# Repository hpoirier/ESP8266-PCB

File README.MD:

Multi application PCB

PCB based on ESP8266 for
- Weather Station: low consumption, can be put in deep sleep and wake up at regular intervals or on an event
- Relay control, for roller blinds for example

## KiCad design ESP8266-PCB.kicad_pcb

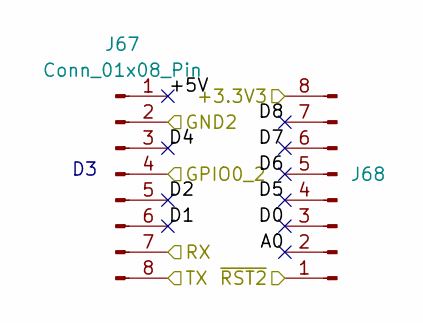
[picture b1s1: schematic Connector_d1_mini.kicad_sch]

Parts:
J67, J68: Conn_01x08_Pin; PinHeader_1x08_P2.54mm_Vertical

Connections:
/+3.3V3: J68.8; also elsewhere on the board
/Connector_d1_mini/+5V: J67.1
/Connector_d1_mini/A0: J68.2
/Connector_d1_mini/D0: J68.3
/Connector_d1_mini/D1: J67.6
/Connector_d1_mini/D2: J67.5
/Connector_d1_mini/D4: J67.3
/Connector_d1_mini/D5: J68.4
/Connector_d1_mini/D6: J68.5
/Connector_d1_mini/D7: J68.6
/Connector_d1_mini/D8: J68.7
/GND2: J67.2; also elsewhere on the board
/GPIO0_2: J67.4; also elsewhere on the board
/RX: J67.7; also elsewhere on the board
/TX: J67.8; also elsewhere on the board
/~RST2: J68.1; also elsewhere on the board

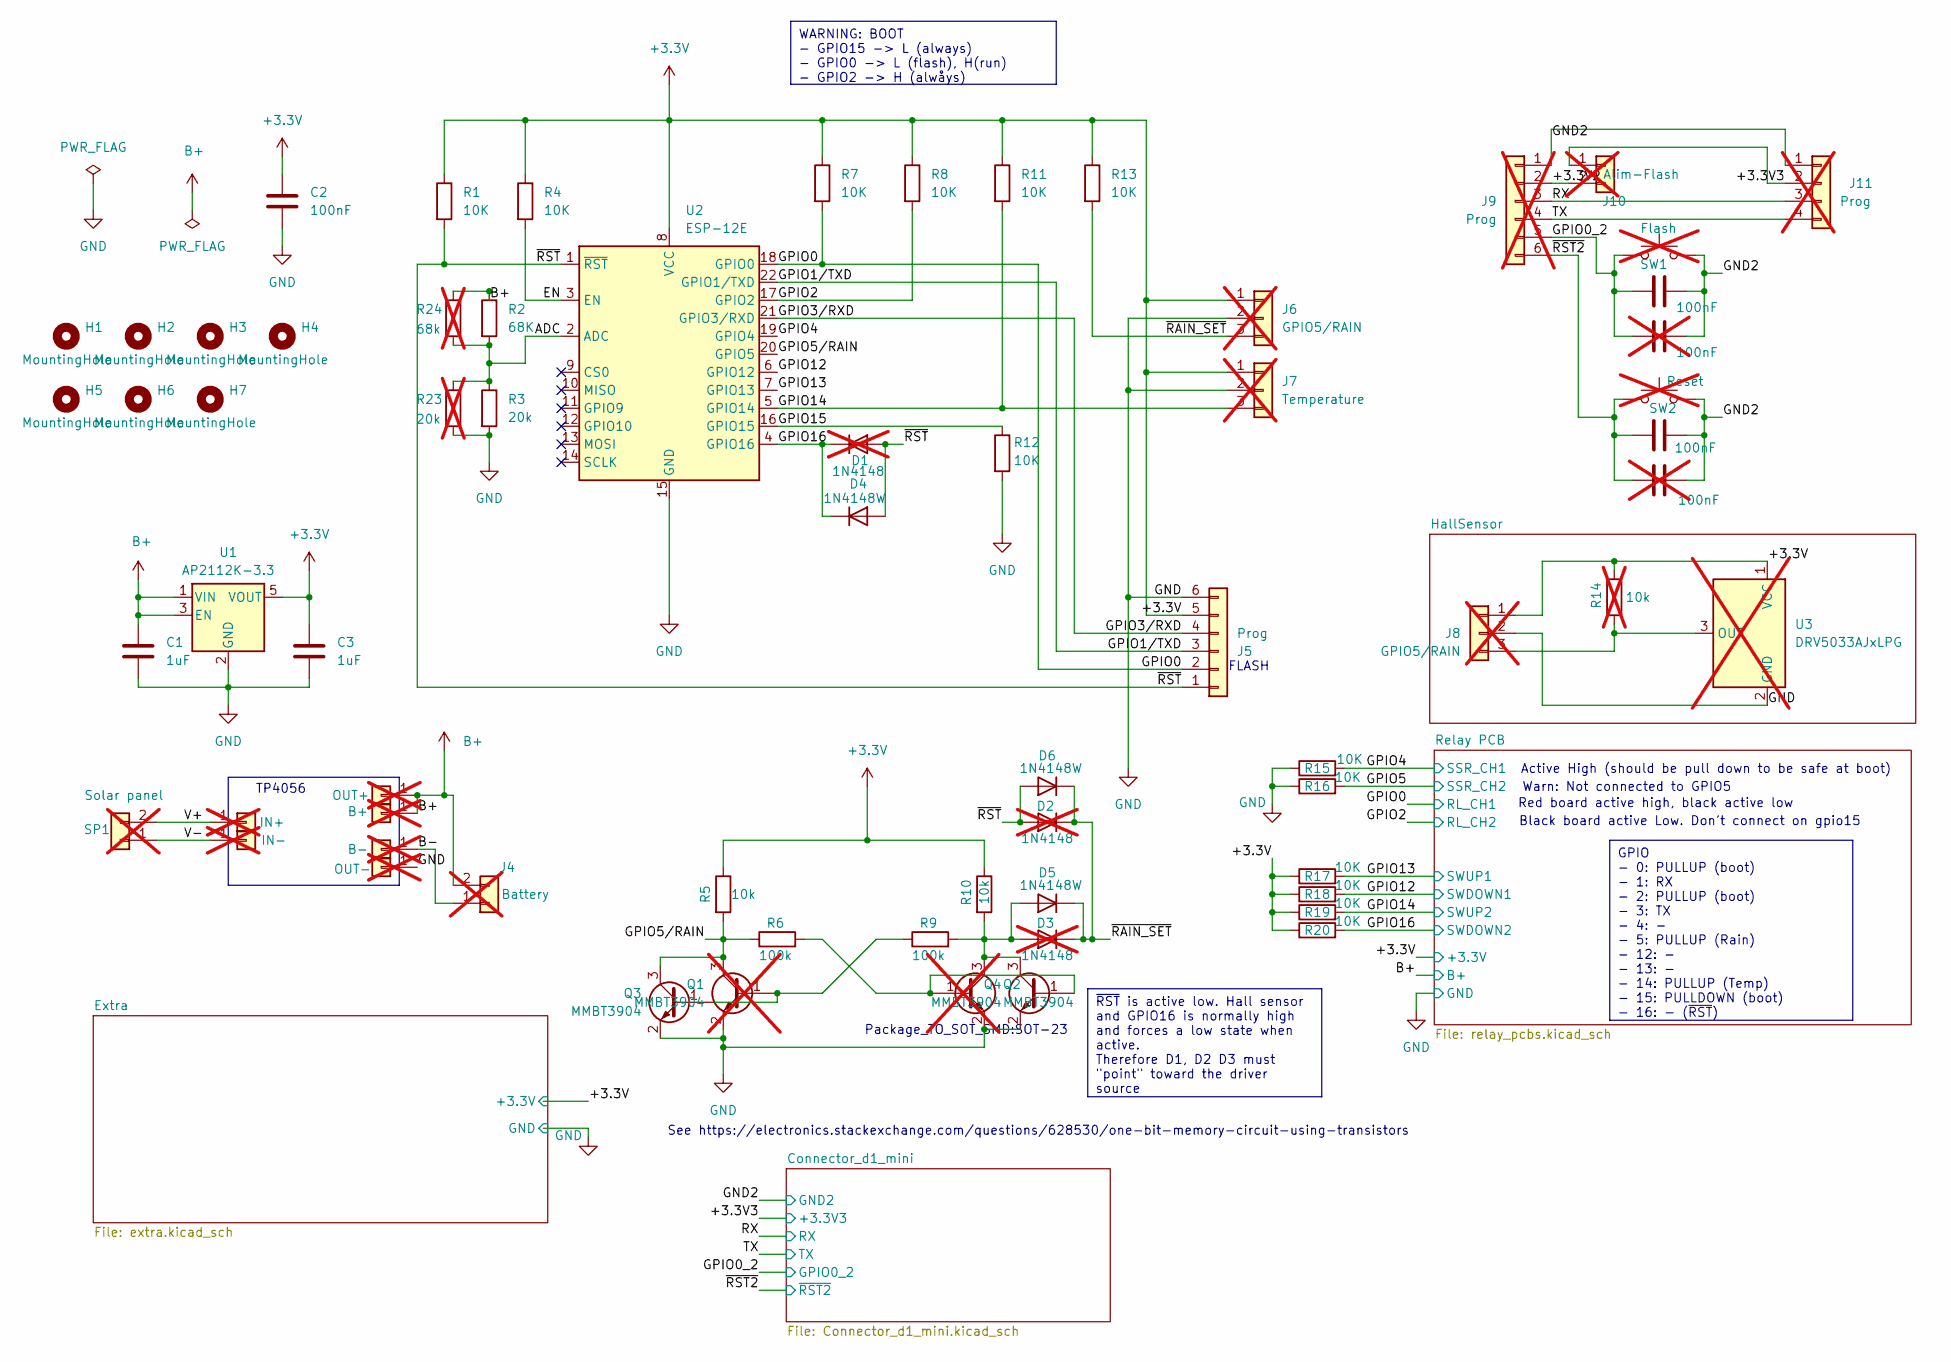
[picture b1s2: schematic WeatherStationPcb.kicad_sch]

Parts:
C1, C3: 1uF; C_1206_3216Metric_Pad1.33x1.80mm_HandSolder
C2: 100nF; C_Disc_D4.7mm_W2.5mm_P5.00mm
C4, C5: 100nF; C_1206_3216Metric_Pad1.33x1.80mm_HandSolder
C8, C9: 100nF; C_Disc_D9.0mm_W2.5mm_P5.00mm; not fitted
D1, D2, D3: 1N4148; D_DO-35_SOD27_P7.62mm_Horizontal; not fitted
D4, D5, D6: 1N4148W; D_SOD-123
H1, H2, H3, H4, H5, H6, H7: MountingHole; MountingHole_2.2mm_M2
J1: IN-; PinSocket_1x01_P2.54mm_Vertical; not fitted
J2: B+; PinSocket_1x01_P2.54mm_Vertical; not fitted
J3: B-; PinSocket_1x01_P2.54mm_Vertical; not fitted
J4: Battery; PinSocket_1x02_P2.54mm_Vertical; not fitted
J5: Prog; PinHeader_1x06_P2.54mm_Vertical
J6, J8: GPIO5/RAIN; PinSocket_1x03_P2.54mm_Vertical; not fitted
J7: Temperature; PinSocket_1x03_P2.54mm_Vertical; not fitted
J9: Prog; PinSocket_1x06_P2.54mm_Vertical; not fitted
J10: Alim-Flash; PinSocket_1x02_P2.54mm_Vertical; not fitted
J11: Prog; PinHeader_1x04_P2.54mm_Vertical; not fitted
J74: OUT-; PinSocket_1x01_P2.54mm_Vertical; not fitted
J75: OUT+; PinSocket_1x01_P2.54mm_Vertical; not fitted
Q1, Q2: MMBT3904; TO-92; not fitted
Q3, Q4: MMBT3904; SOT-23_Handsoldering
R1, R4, R7, R8, R12, R13, R15, R16, R17, R18, R19, R20: 10K; R_1206_3216Metric_Pad1.30x1.75mm_HandSolder
R2: 68K; R_0805_2012Metric_Pad1.20x1.40mm_HandSolder
R3: 20k; R_0805_2012Metric_Pad1.20x1.40mm_HandSolder
R5, R10: 10k; R_1206_3216Metric_Pad1.30x1.75mm_HandSolder
R6, R9: 100k; R_1206_3216Metric_Pad1.30x1.75mm_HandSolder
R11: 10K; R_Axial_DIN0204_L3.6mm_D1.6mm_P7.62mm_Horizontal
R14: 10k; not fitted
R23: 20k; R_Axial_DIN0204_L3.6mm_D1.6mm_P7.62mm_Horizontal; not fitted
R24: 68k; R_Axial_DIN0204_L3.6mm_D1.6mm_P7.62mm_Horizontal; not fitted
SP1: Solar panel; PinSocket_1x02_P2.54mm_Vertical; not fitted
SP2: IN+; PinSocket_1x01_P2.54mm_Vertical; not fitted
SW1: Flash; SW_PUSH_6mm_H4.3mm; not fitted
SW2: Reset; SW_PUSH_6mm_H4.3mm; not fitted
U1: AP2112K-3.3; SOT-23-5_HandSoldering
U2: ESP-12E
U3: DRV5033AJxLPG; TO-92_Inline; not fitted

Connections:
+3.3V: C2.1, C3.1, J5.5, J6.1, J7.1, J8.1, R1.1, R4.1, R5.1, R7.1, R8.1, R10.1, R11.1, R13.1, R14.1, R17.1, R18.1, R19.1, R20.1, U1.5 (VOUT), U2.8 (VCC), U3.1 (VCC); also elsewhere on the board
/+3.3V2: J9.2, J10.2
/+3.3V3: J10.1, J11.2; also elsewhere on the board
/ADC: R2.2, R3.1, R23.1, R24.2, U2.2 (ADC)
/B-: J3.1, J4.1
/EN: R4.2, U2.3 (EN)
/GND2: C4.1, C5.2, C8.1, C9.1, J9.1, J11.1, SW1.2, SW2.2; also elsewhere on the board
/GPIO0: J5.2, R7.2, U2.18 (GPIO0); also elsewhere on the board
/GPIO0_2: C4.2, C8.2, J9.5, SW1.1; also elsewhere on the board
/GPIO1/TXD: J5.3, U2.22 (GPIO1/TXD)
/GPIO2: R8.2, U2.17 (GPIO2); also elsewhere on the board
/GPIO3/RXD: J5.4, U2.21 (GPIO3/RXD)
/GPIO4: R15.2, U2.19 (GPIO4); also elsewhere on the board
/GPIO5: R16.2; also elsewhere on the board
/GPIO5/RAIN: Q1.3 (C), Q3.3 (C), R5.2, R6.1, U2.20 (GPIO5)
/GPIO12: R18.2, U2.6 (GPIO12); also elsewhere on the board
/GPIO13: R17.2, U2.7 (GPIO13); also elsewhere on the board
/GPIO14: J7.3, R11.2, R19.2, U2.5 (GPIO14); also elsewhere on the board
/GPIO15: R12.1, U2.16 (GPIO15)
/GPIO16: D1.1 (K), D4.1 (K), R20.2, U2.4 (GPIO16); also elsewhere on the board
/RX: J9.3, J11.3; also elsewhere on the board
/TX: J9.4, J11.4; also elsewhere on the board
/V+: SP1.2, SP2.1
/V-: J1.1, SP1.1
/~RAIN_SET: D2.1 (K), D3.1 (K), D5.1 (K), D6.1 (K), J6.3, R13.2
/~RST2: C5.1, C9.2, J9.6, SW2.1; also elsewhere on the board
/~RST: D1.2 (A), D2.2 (A), D4.2 (A), D6.2 (A), J5.1, R1.2, U2.1 (~RST)
B+: C1.1, J2.1, J4.2, J75.1, R2.1, R24.1, U1.1 (VIN), U1.3 (EN); also elsewhere on the board
GND: C1.2, C2.2, C3.2, J5.6, J6.2, J7.2, J8.2, J74.1, Q1.2 (E), Q2.2 (E), Q3.2 (E), Q4.2 (E), R3.2, R12.2, R15.1, R16.1, R23.2, U1.2 (GND), U2.15 (GND), U3.2 (GND); also elsewhere on the board
unnamed: D3.2 (A), D5.2 (A), Q2.3 (C), Q4.3 (C), R9.2, R10.2
unnamed: J8.3, R14.2, U3.3 (OUT)
unnamed: Q1.1 (B), Q3.1 (B), R9.1
unnamed: Q2.1 (B), Q4.1 (B), R6.2

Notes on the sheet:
WARNING: BOOT - GPIO15 -> L (always) - GPIO0 -> L (flash), H(run) - GPIO2 -> H (alwåys)
GPIO - 0: PULLUP (boot) - 1: RX - 2: PULLUP (boot) - 3: TX - 4: - - 5: PULLUP (Rain) - 12: - - 13: - - 14: PULLUP (Temp) - 15: PULLDOWN (boot) - 16: - (~{RST})
~{RST} is active low. Hall sensor and GPIO16 is normally high and forces a low state when active. Therefore D1, D2 D3 must "point" toward the driver source
Active High (should be pull down to be safe at boot)
Package_TO_SOT_SMD:SOT-23
Red board active high, black active low
Black board active Low. Don't connect on gpio15
FLASH
See https://electronics.stackexchange.com/questions/628530/one-bit-memory-circuit-using-transistors
TP4056
Warn: Not connected to GPIO5

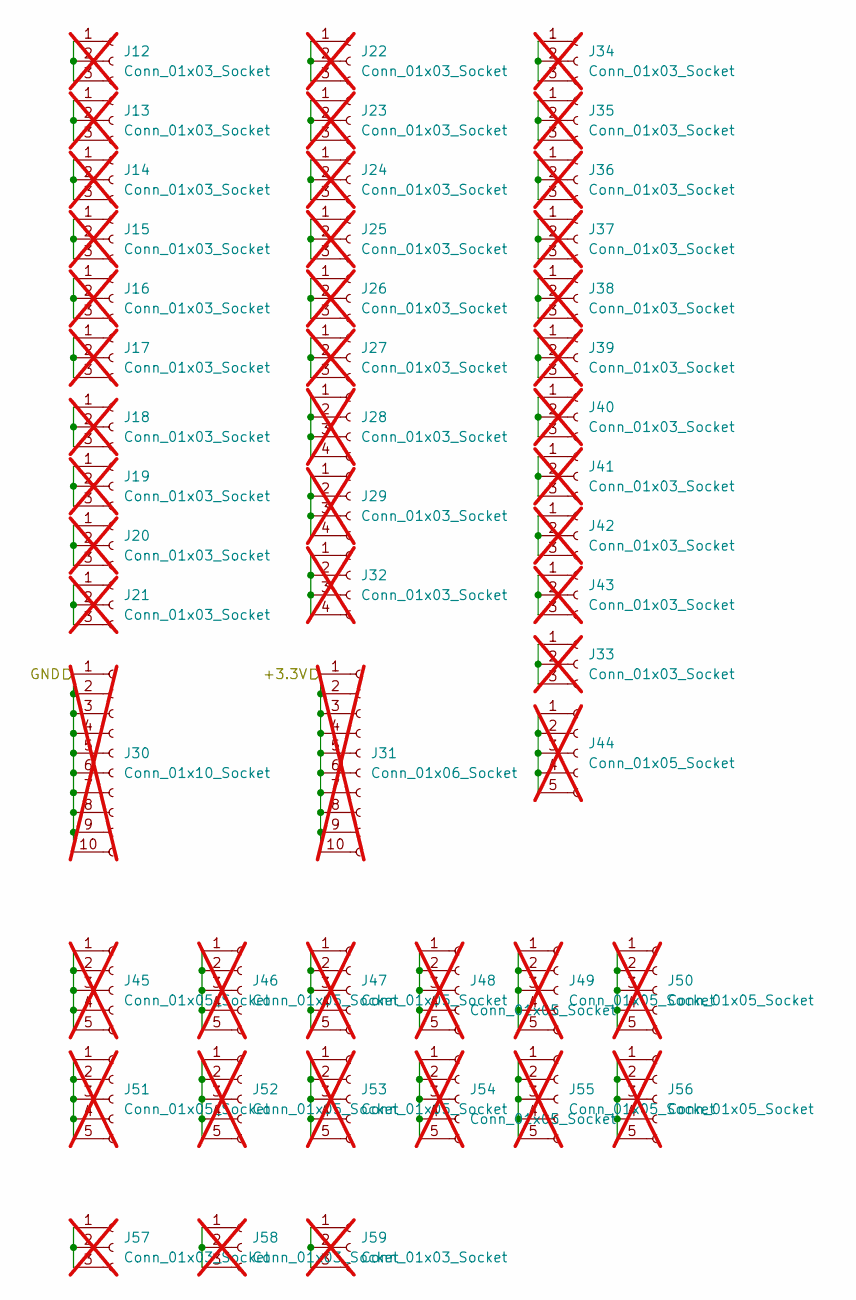
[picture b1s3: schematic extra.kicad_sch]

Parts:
J12, J13, J14, J15, J16, J17, J18, J19, J20, J21, J22, J23, J24, J25, J26, J27, J33, J34, J35, J36, J37, J38, J39, J40, J41, J42, J43, J57, J58, J59: Conn_01x03_Socket; PinSocket_1x03_P2.54mm_Vertical; not fitted
J28, J29, J32: Conn_01x03_Socket; PinSocket_1x04_P2.54mm_Vertical; not fitted
J30: Conn_01x10_Socket; PinSocket_1x10_P2.54mm_Vertical; not fitted
J31: Conn_01x06_Socket; PinSocket_1x10_P2.54mm_Vertical; not fitted
J44, J45, J46, J47, J48, J49, J50, J51, J52, J53, J54, J55, J56: Conn_01x05_Socket; PinSocket_1x05_P2.54mm_Vertical; not fitted

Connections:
+3.3V: J31.1, J31.2, J31.3, J31.4, J31.5, J31.6, J31.7, J31.8, J31.9, J31.10; also elsewhere on the board
GND: J30.1, J30.2, J30.3, J30.4, J30.5, J30.6, J30.7, J30.8, J30.9, J30.10; also elsewhere on the board
unnamed: J12.1, J12.2, J12.3
unnamed: J13.1, J13.2, J13.3
unnamed: J14.1, J14.2, J14.3
unnamed: J15.1, J15.2, J15.3
unnamed: J16.1, J16.2, J16.3
unnamed: J17.1, J17.2, J17.3
unnamed: J18.1, J18.2, J18.3
unnamed: J19.1, J19.2, J19.3
unnamed: J20.1, J20.2, J20.3
unnamed: J21.1, J21.2, J21.3
unnamed: J22.1, J22.2, J22.3
unnamed: J23.1, J23.2, J23.3
unnamed: J24.1, J24.2, J24.3
unnamed: J25.1, J25.2, J25.3
unnamed: J26.1, J26.2, J26.3
unnamed: J27.1, J27.2, J27.3
unnamed: J28.1, J28.2, J28.3, J28.4
unnamed: J29.1, J29.2, J29.3, J29.4
unnamed: J32.1, J32.2, J32.3, J32.4
unnamed: J33.1, J33.2, J33.3
unnamed: J34.1, J34.2, J34.3
unnamed: J35.1, J35.2, J35.3
unnamed: J36.1, J36.2, J36.3
unnamed: J37.1, J37.2, J37.3
unnamed: J38.1, J38.2, J38.3
unnamed: J39.1, J39.2, J39.3
unnamed: J40.1, J40.2, J40.3
unnamed: J41.1, J41.2, J41.3
unnamed: J42.1, J42.2, J42.3
unnamed: J43.1, J43.2, J43.3
unnamed: J44.1, J44.2, J44.3, J44.4, J44.5
unnamed: J45.1, J45.2, J45.3, J45.4, J45.5
unnamed: J46.1, J46.2, J46.3, J46.4, J46.5
unnamed: J47.1, J47.2, J47.3, J47.4, J47.5
unnamed: J48.1, J48.2, J48.3, J48.4, J48.5
unnamed: J49.1, J49.2, J49.3, J49.4, J49.5
unnamed: J50.1, J50.2, J50.3, J50.4, J50.5
unnamed: J51.1, J51.2, J51.3, J51.4, J51.5
unnamed: J52.1, J52.2, J52.3, J52.4, J52.5
unnamed: J53.1, J53.2, J53.3, J53.4, J53.5
unnamed: J54.1, J54.2, J54.3, J54.4, J54.5
unnamed: J55.1, J55.2, J55.3, J55.4, J55.5
unnamed: J56.1, J56.2, J56.3, J56.4, J56.5
unnamed: J57.1, J57.2, J57.3
unnamed: J58.1, J58.2, J58.3
unnamed: J59.1, J59.2, J59.3

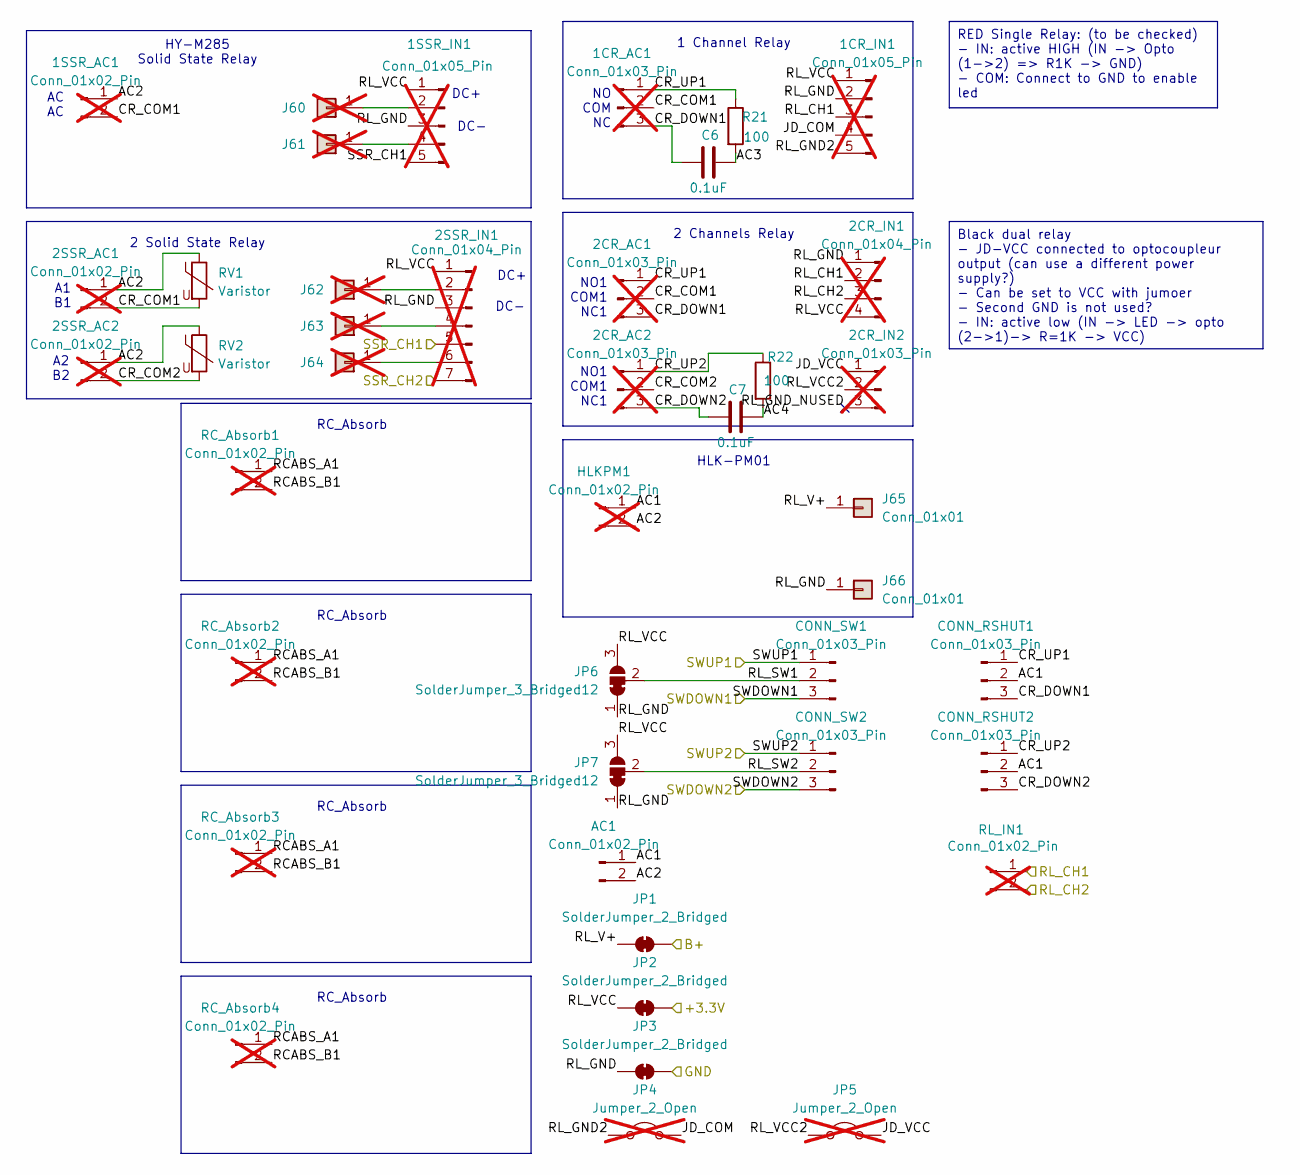
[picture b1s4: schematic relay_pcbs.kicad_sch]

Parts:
1CR_AC1, 2CR_AC1, 2CR_AC2: Conn_01x03_Pin; TerminalBlock_Phoenix_MKDS-1,5-3-5.08_1x03_P5.08mm_Horizont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; not fitted
1CR_IN1, 1SSR_IN1: Conn_01x05_Pin; PinHeader_1x05_P2.54mm_Vertical; not fitted
1SSR_AC1, 2SSR_AC1, 2SSR_AC2: Conn_01x02_Pin; TerminalBlock_Phoenix_MKDS-1,5-2-5.08_1x02_P5.08mm_Horizont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; not fitted
2CR_IN1: Conn_01x04_Pin; PinHeader_1x04_P2.54mm_Vertical; not fitted
2CR_IN2: Conn_01x03_Pin; PinHeader_1x03_P2.54mm_Vertical; not fitted
2SSR_IN1: Conn_01x04_Pin; PinHeader_1x07_P2.54mm_Vertical; not fitted
AC1: Conn_01x02_Pin; TerminalBlock_Phoenix_MKDS-1,5-2-5.08_1x02_P5.08mm_Horizont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
C6, C7: 0.1uF; C_Axial_L12.0mm_D6.5mm_P15.00mm_Horizontal
CONN_RSHUT1, CONN_RSHUT2: Conn_01x03_Pin; TerminalBlock_Phoenix_MKDS-1,5-3-5.08_1x03_P5.08mm_Horizont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
CONN_SW1, CONN_SW2: Conn_01x03_Pin; TerminalBlock_Phoenix_MKDS-1,5-3-5.08_1x03_P5.08mm_Horizont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
HLKPM1: Conn_01x02_Pin; TerminalBlock_Phoenix_MKDS-1,5-2-5.08_1x02_P5.08mm_Horizont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; not fitted
J60, J61, J62, J63, J64: Conn_01x01; PinSocket_1x01_P2.54mm_Vertical; not fitted
J65, J66: Conn_01x01; PinHeader_1x01_P2.54mm_Vertical
JP1, JP2, JP3: SolderJumper_2_Bridged; SolderJumper-2_P1.3mm_Bridged_RoundedPad1.0x1.5mm
JP4, JP5: Jumper_2_Open; PinHeader_1x02_P2.54mm_Vertical; not fitted
JP6, JP7: SolderJumper_3_Bridged12; SolderJumper-3_P1.3mm_Bridged12_RoundedPad1.0x1.5mm_NumberL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
R21, R22: 100; R_Axial_DIN0414_L11.9mm_D4.5mm_P15.24mm_Horizontal
RC_Absorb1, RC_Absorb2, RC_Absorb3, RC_Absorb4: Conn_01x02_Pin; TerminalBlock_Phoenix_MKDS-1,5-2-5.08_1x02_P5.08mm_Horizont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; not fitted
RL_IN1: Conn_01x02_Pin; PinHeader_1x02_P2.54mm_Vertical; not fitted
RV1, RV2: Varistor; RV_Disc_D12mm_W4.5mm_P7.5mm

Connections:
+3.3V: JP2.2 (B); also elsewhere on the board
/GPIO0: 1CR_IN1.3, 2CR_IN1.2, RL_IN1.1; also elsewhere on the board
/GPIO2: 2CR_IN1.3, RL_IN1.2; also elsewhere on the board
/GPIO4: 1SSR_IN1.5, 2SSR_IN1.5; also elsewhere on the board
/GPIO5: 2SSR_IN1.7; also elsewhere on the board
/GPIO12: CONN_SW1.3; also elsewhere on the board
/GPIO13: CONN_SW1.1; also elsewhere on the board
/GPIO14: CONN_SW2.1; also elsewhere on the board
/GPIO16: CONN_SW2.3; also elsewhere on the board
/Relay PCB/AC1: AC1.1, CONN_RSHUT1.2, CONN_RSHUT2.2, HLKPM1.1
/Relay PCB/AC2: 1SSR_AC1.1, 2SSR_AC1.1, 2SSR_AC2.1, AC1.2, HLKPM1.2, RV1.1, RV2.1
/Relay PCB/AC3: C6.2, R21.2
/Relay PCB/AC4: C7.2, R22.2
/Relay PCB/CR_COM1: 1CR_AC1.2, 1SSR_AC1.2, 2CR_AC1.2, 2SSR_AC1.2, RV1.2
/Relay PCB/CR_COM2: 2CR_AC2.2, 2SSR_AC2.2, RV2.2
/Relay PCB/CR_DOWN1: 1CR_AC1.3, 2CR_AC1.3, C6.1, CONN_RSHUT1.3
/Relay PCB/CR_DOWN2: 2CR_AC2.3, C7.1, CONN_RSHUT2.3
/Relay PCB/CR_UP1: 1CR_AC1.1, 2CR_AC1.1, CONN_RSHUT1.1, R21.1
/Relay PCB/CR_UP2: 2CR_AC2.1, CONN_RSHUT2.1, R22.1
/Relay PCB/JD_COM: 1CR_IN1.4, JP4.2 (B)
/Relay PCB/JD_VCC: 2CR_IN2.1, JP5.2 (B)
/Relay PCB/RL_GND: 1CR_IN1.2, 1SSR_IN1.3, 2CR_IN1.1, 2SSR_IN1.3, J66.1, JP3.1 (A), JP6.1 (A), JP7.1 (A)
/Relay PCB/RL_GND2: 1CR_IN1.5, JP4.1 (A)
/Relay PCB/RL_GND_NUSED: 2CR_IN2.3
/Relay PCB/RL_SW1: CONN_SW1.2, JP6.2 (C)
/Relay PCB/RL_SW2: CONN_SW2.2, JP7.2 (C)
/Relay PCB/RL_V+: J65.1, JP1.1 (A)
/Relay PCB/RL_VCC: 1CR_IN1.1, 1SSR_IN1.1, 2CR_IN1.4, 2SSR_IN1.1, JP2.1 (A), JP6.3 (B), JP7.3 (B)
/Relay PCB/RL_VCC2: 2CR_IN2.2, JP5.1 (A)
B+: JP1.2 (B); also elsewhere on the board
GND: JP3.2 (B); also elsewhere on the board
unnamed: 1SSR_IN1.2, J60.1
unnamed: 1SSR_IN1.4, J61.1
unnamed: 2SSR_IN1.2, J62.1
unnamed: 2SSR_IN1.4, J63.1
unnamed: 2SSR_IN1.6, J64.1
unnamed: RC_Absorb1.1, RC_Absorb2.1, RC_Absorb3.1, RC_Absorb4.1
unnamed: RC_Absorb1.2, RC_Absorb2.2, RC_Absorb3.2, RC_Absorb4.2

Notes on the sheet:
Black dual relay - JD-VCC connected to optocoupleur output (can use a different power supply?) - Can be set to VCC with jumoer - Second GND is not used? - IN: active low (IN -> LED -> opto (2->1)-> R=1K -> VCC)
RED Single Relay: (to be checked) - IN: active HIGH (IN -> Opto (1->2) => R1K -> GND) - COM: Connect to GND to enable led
NO1 COM1 NC1
NO COM NC
RC_Absorb
DC+
2 Channels Relay
DC-
2 Solid State Relay
A2 B2
HY-M285 Solid State Relay
AC AC
1 Channel Relay
A1 B1
HLK-PM01

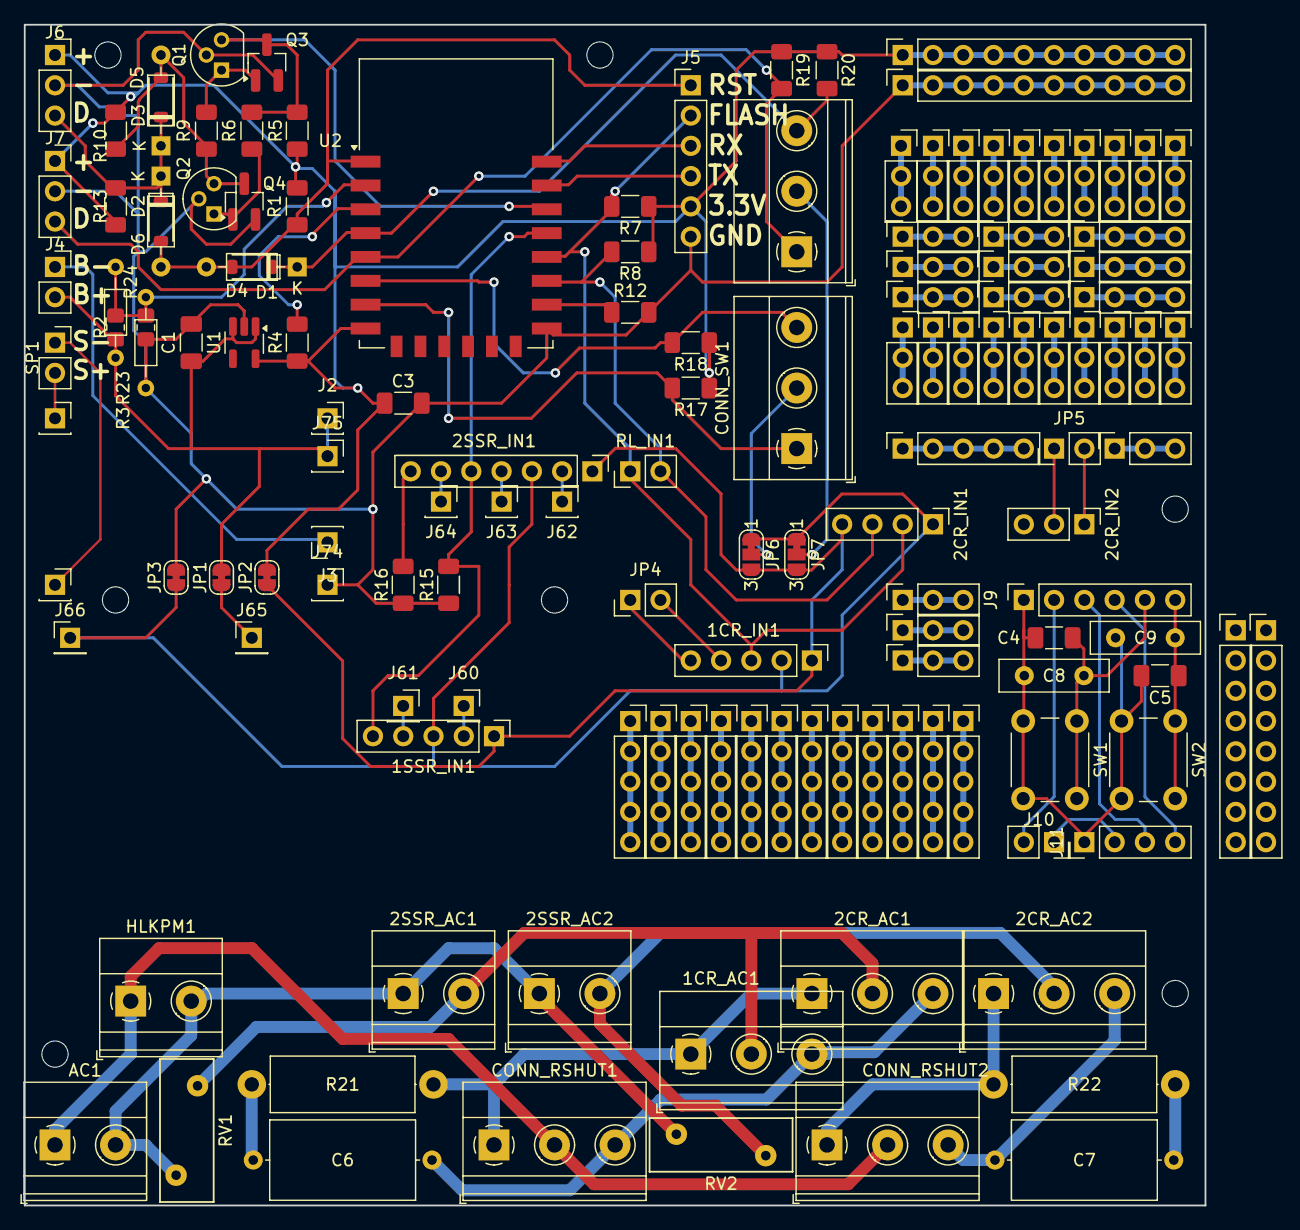
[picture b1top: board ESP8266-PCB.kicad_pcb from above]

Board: 2 copper layers, 99.1 x 99.1 mm, 148 parts (0 on the bottom side), 102 nets.

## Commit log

2026-02-28 first import
2026-02-28 Project renamed in ESP8266-PCB
2026-02-28 Removed old files
